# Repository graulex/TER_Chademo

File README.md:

# Projet TER – Communication CAN avec STM32 pour la recharge CHAdeMO

##  Introduction

Ce dépôt GitHub présente le travail réalisé dans le cadre du **projet TER** intitulé :

**_Conception de cartes de communication CAN sur la base d’un microcontrôleur STM32 pour l’émulation de la gestion de charge de la voiture électrique avec le protocole CHAdeMO._**

Ce projet a été mené par :

- **Alexandre Guilcher**  
- **Damien Gonfo**  
- **Salah Ouaret**  

Sous la direction de **Damian Sal y Rosas**.

---

##  Organisation du dépôt

### `code/`
Contient l'ensemble des codes sources du projet :
-  **Code C STM32 - Borne de recharge (EVSE)** : développé avec STM32CubeIDE, implémente la logique de communication CHAdeMO côté borne.
-  **Code C STM32 - Véhicule électrique (EV)** : développé également sur STM32CubeIDE, simule le comportement d’un véhicule compatible CHAdeMO.
-  **Interface MATLAB** : IHM développée sous MATLAB permettant de communiquer avec la borne via une interface série (USART). Elle permet de lancer ou arrêter la charge et de suivre l’état de la batterie depuis un ordinateur.

---

### `documentation/`
Regroupe les ressources techniques utilisées :
-  **Articles scientifiques**
-  **Documentation technique officielle IEEE**

---

### `doxygen/`
Documentation logicielle générée automatiquement avec **Doxygen** :  
Décrit les fonctions, structures et comportements du code C (borne et véhicule).

---

### `uml/`
Diagrammes UML utilisés pendant la phase de conception :
- Diagrammes de cas d’usage
- Diagrammes de séquence
- Diagrammes de classes pour le logiciel embarqué de la borne et du véhicule
- Machines à états du véhicule et de la borne

---

### `kicad/`
Plans électroniques créés avec **KiCad** :
- 🛠 **Carte Borne de Recharge**
-  **Carte Véhicule Électrique**

Ces schémas permettent la fabrication physique des deux cartes de communication basées sur le protocole CAN.

---

##  Remarques

- Ce projet met en œuvre une **communication CAN bas-niveau**, conforme au protocole **CHAdeMO**, simulée entre une "borne" et un "véhicule" via des cartes STM32.
- L'IHM MATLAB agit comme un **outil de supervision et de contrôle**, permettant de **déclencher** et **suivre** une session de charge.

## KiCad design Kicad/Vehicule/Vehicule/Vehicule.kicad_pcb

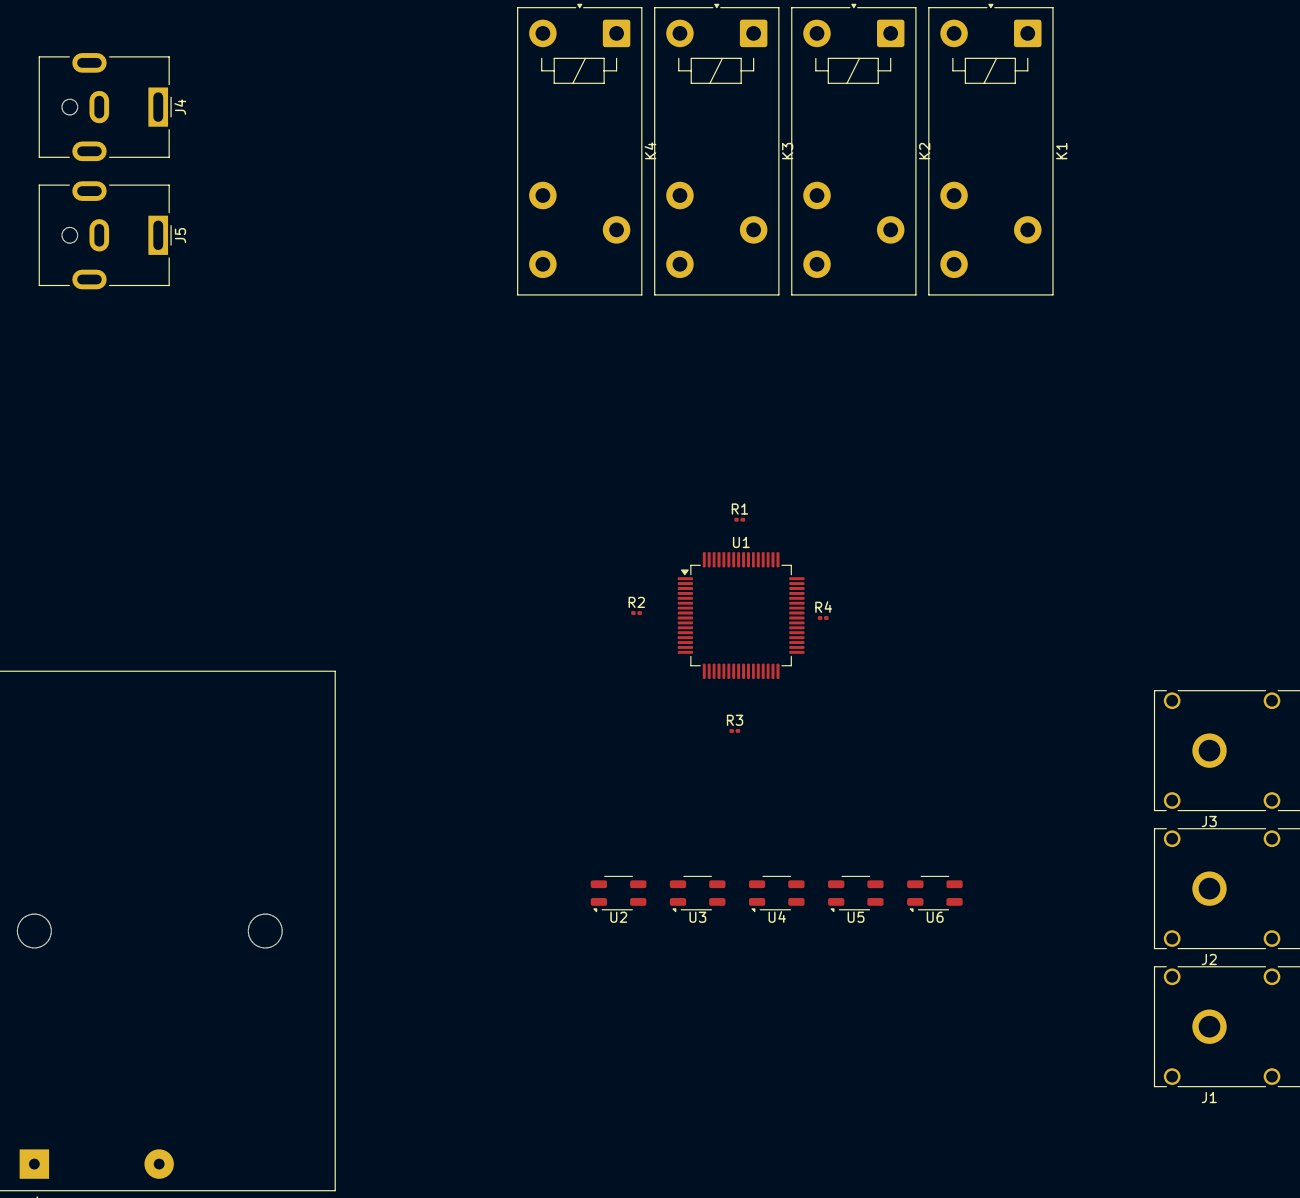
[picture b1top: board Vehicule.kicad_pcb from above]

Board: 2 copper layers, 20 parts (0 on the bottom side), 24 nets, no tracks yet.

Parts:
BT1: Batterie Vehicule; BatteryHolder_Keystone_2479_3xAAA
J1: Connecteur EVSE-Vehicule; Banana_Cliff_FCR7350B_S16N-PC_Horizontal
J2: Plug Charge 1; Banana_Cliff_FCR7350B_S16N-PC_Horizontal
J3: Plug Charge 2; Banana_Cliff_FCR7350B_S16N-PC_Horizontal
J4: Plug Detecteur de Proximite; BarrelJack_CUI_PJ-063AH_Horizontal
J5: Plug Permission de Charge; BarrelJack_CUI_PJ-063AH_Horizontal
K1: Relai de Charge 1 - C1; Relay_SPDT_Finder_40.31
K2: Relai de Charge 2 - C2; Relay_SPDT_Finder_40.31
K3: Relai de Charge 3 - C3; Relay_SPDT_Finder_40.31
K4: Relai de Proximite; Relay_SPDT_Finder_40.31
R1, R2, R3, R4: R; R_0201_0603Metric
U1: STM32L4A6RGTx; LQFP-64_10x10mm_P0.5mm
U2: Optocoupleur Vehicule 1; OnSemi_CASE100CY
U3: Optocoupleur Vehicule 2; OnSemi_CASE100CY
U4: Optocoupleur Proximite 1; OnSemi_CASE100CY
U5: Optocoupleur Proximite 2; OnSemi_CASE100CY
U6: Optocoupleur Permission de Charge; OnSemi_CASE100CY

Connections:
+12V: K4.A1, U4.1 (A)
GND: U2.2 (K), U5.2 (K), U6.4 (R)
unnamed: J1.1, K2.14
unnamed: J2.1, K1.A1, K2.A1, R2.2, U3.1 (A)
unnamed: J3.1, K3.14, R3.2
unnamed: J4.1, R4.2
unnamed: J5.1, R1.2
unnamed: K1.A2, K2.A2
unnamed: K4.14, R4.1
unnamed: R1.1, U6.3 (R)
unnamed: U1.17 (PA3), U6.1 (A)
unnamed: U1.20 (PA4), U6.2 (K)
unnamed: U1.21 (PA5), U5.3 (R)
unnamed: U1.22 (PA6), U5.4 (R)
unnamed: U1.23 (PA7), U4.3 (R)
unnamed: U1.41 (PA8), U4.4 (R)
unnamed: U1.42 (PA9), U3.3 (R)
unnamed: U1.43 (PA10), U3.4 (R)
unnamed: U1.44 (PA11), U2.3 (R)
unnamed: U1.45 (PA12), U2.4 (R)
unnamed: U1.18 (VSS), U1.31 (VSS), U1.47 (VSS), U1.63 (VSS)
unnamed: R2.1, U2.1 (A)
unnamed: R3.1, U3.2 (K)
unnamed: K4.A2, U5.1 (A)

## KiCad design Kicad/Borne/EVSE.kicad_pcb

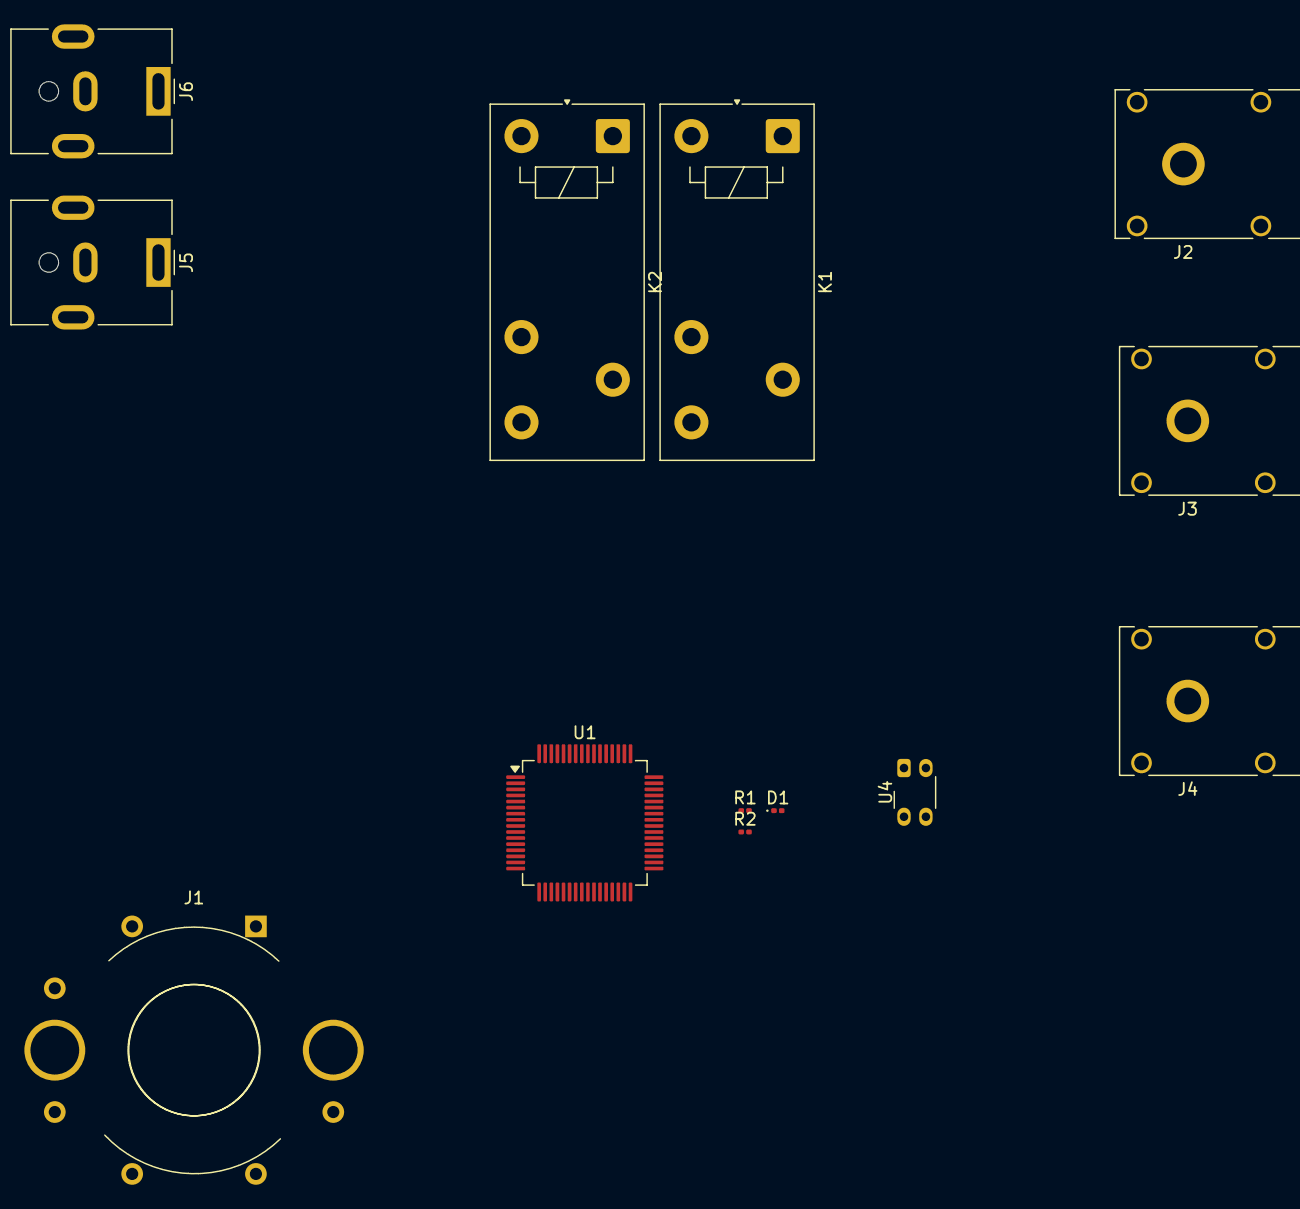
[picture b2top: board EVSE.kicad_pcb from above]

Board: 2 copper layers, 13 parts (0 on the bottom side), 14 nets, no tracks yet.

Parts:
D1: D; LED_0201_0603Metric
J1: Reseau EDF; Valve_Mini_G
J2: Connecteur EVSE-Vehicule; Banana_Cliff_FCR7350B_S16N-PC_Horizontal
J3: Plug Charge 1; Banana_Cliff_FCR7350B_S16N-PC_Horizontal
J4: Plug Charge 2; Banana_Cliff_FCR7350B_S16N-PC_Horizontal
J5: Plug Detecteur de proximite; BarrelJack_CUI_PJ-063AH_Horizontal
J6: Plug Permission de Charge; BarrelJack_CUI_PJ-063AH_Horizontal
K1: Relai Charge 1 - D1; Relay_SPDT_Finder_40.31
K2: Relai Charge 2 - D2; Relay_SPDT_Finder_40.31
R1, R2: R; R_0201_0603Metric
U1: STM32L476RGTx; LQFP-64_10x10mm_P0.5mm
U4: Optocoupleur; Kodenshi_SG105F

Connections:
Chargeur +12V: K1.14, U4.2 (K)
Earth: J1.3, K2.14, R1.1
unnamed: D1.2 (A), J1.2
unnamed: D1.1 (K), J2.1
unnamed: J5.1, R1.2
unnamed: J6.1, R2.2
unnamed: K1.A1, U1.20 (PA4)
unnamed: K1.A2, U1.22 (PA6)
unnamed: K2.A1, U1.23 (PA7)
unnamed: K2.A2, U1.41 (PA8)
unnamed: U1.42 (PA9), U4.3 (R)
unnamed: U1.43 (PA10), U4.4 (R)
unnamed: U1.18 (VSS), U1.31 (VSS), U1.47 (VSS), U1.63 (VSS)
unnamed: R2.1, U4.1 (A)

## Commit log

2025-05-02 Premier commit, code + doxygen + articles
2025-05-03 Ajout de documentation, digrammes UML (MEF) et changement sur Doxygen
2025-05-03 Ajout diapo présentation et code IHM
2025-05-03 Ajout fichiers Kicad
2025-05-05 Ajout diagrammes + compte rendu amélioré
